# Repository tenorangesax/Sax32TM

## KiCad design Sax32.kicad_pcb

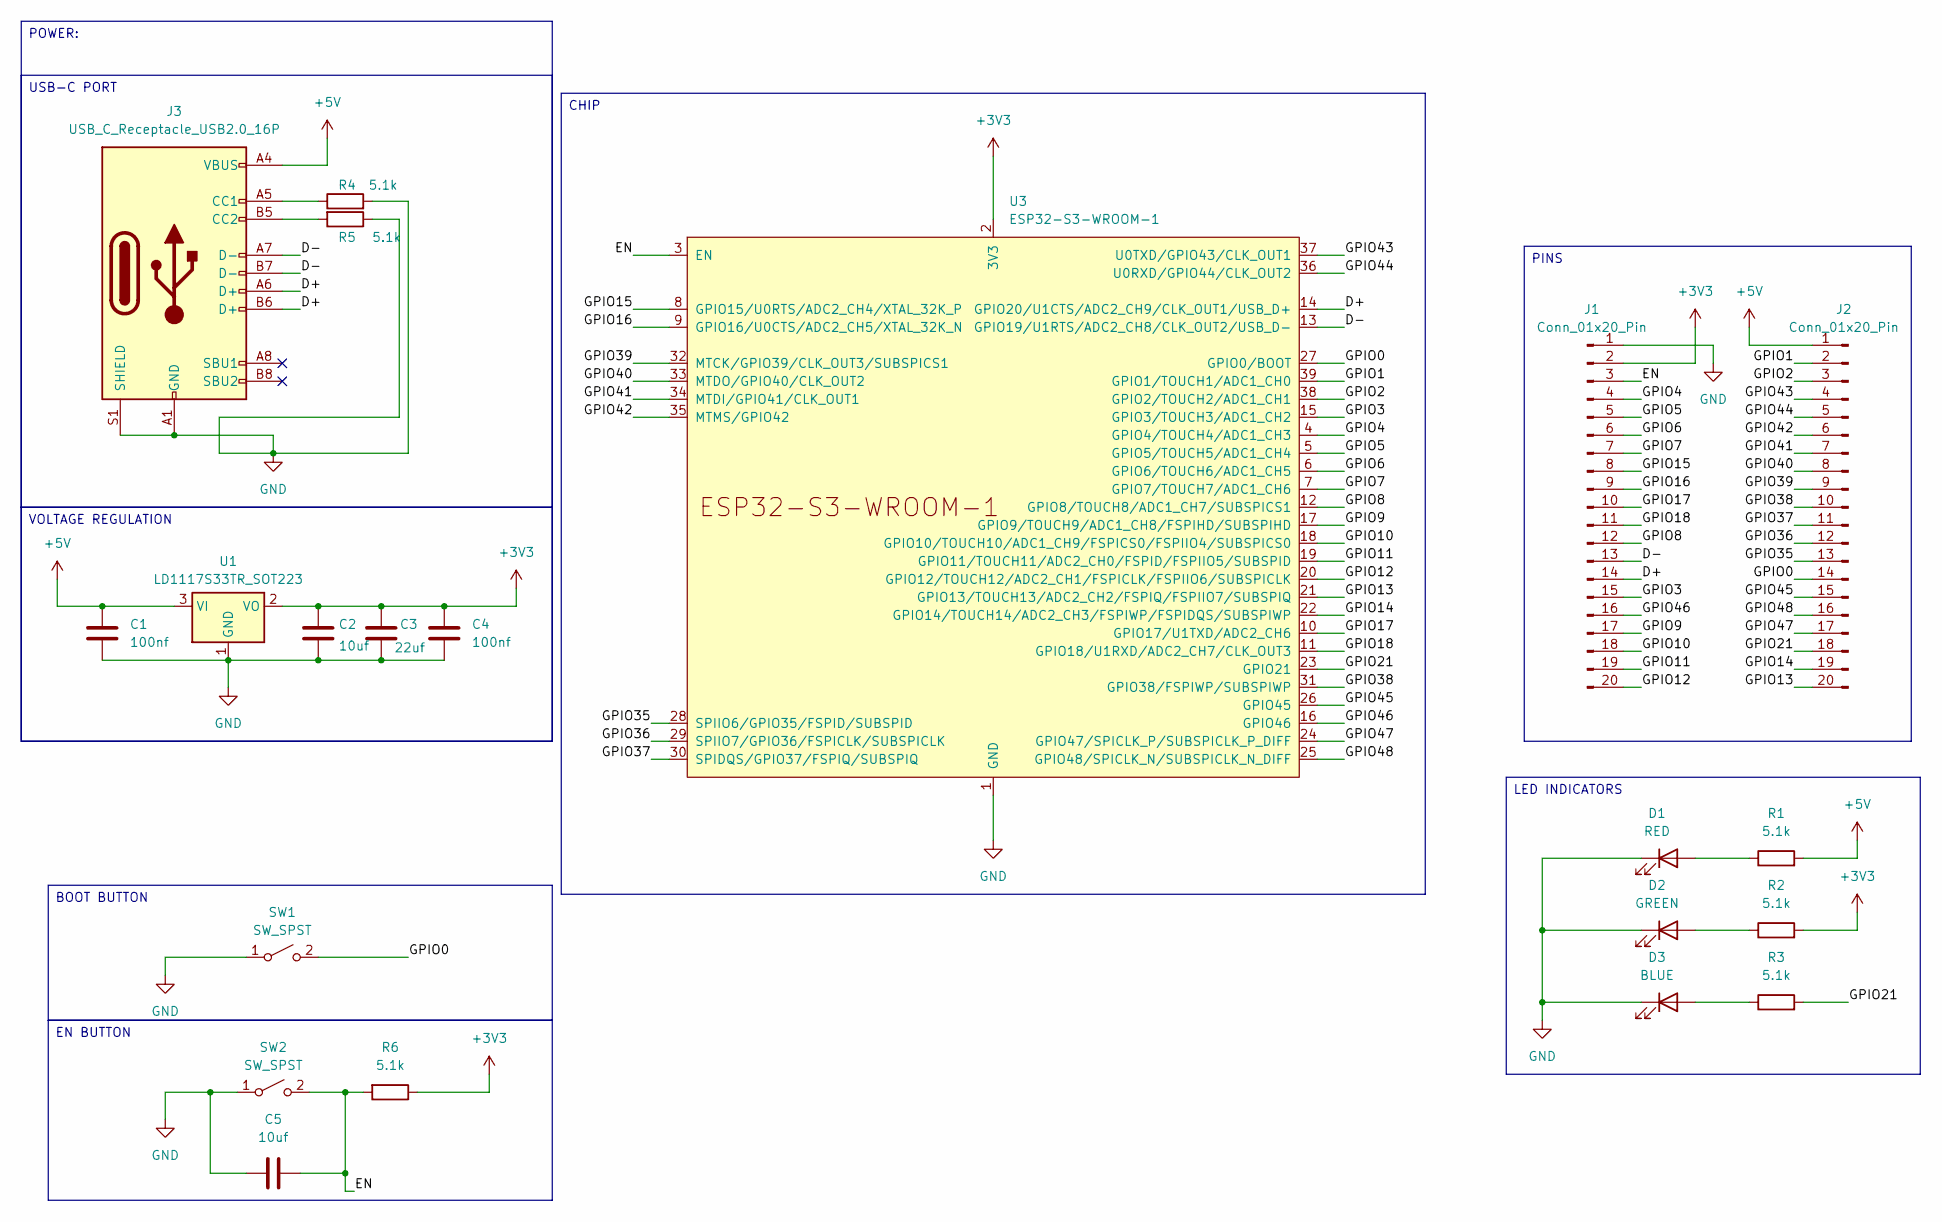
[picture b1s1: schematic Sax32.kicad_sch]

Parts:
C1, C4: 100nf; C_0603_1608Metric
C2, C5: 10uf; C_0603_1608Metric
C3: 22uf; C_0603_1608Metric
D1: RED; LED_0603_1608Metric
D2: GREEN; LED_0603_1608Metric
D3: BLUE; LED_0603_1608Metric
J1, J2: Conn_01x20_Pin; PinHeader_1x20_P2.54mm_Vertical
J3: USB_C_Receptacle_USB2.0_16P; USB_C_Receptacle_HRO_TYPE-C-31-M-12
R1, R2, R3, R4, R5, R6: 5.1k; R_0603_1608Metric
SW1, SW2: SW_SPST; SW_Push_SPST_NO_Alps_SKRK
U1: LD1117S33TR_SOT223; SOT-223-3_TabPin2
U3: ESP32-S3-WROOM-1

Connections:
+3V3: C2.1, C3.1, C4.1, J1.2, R2.2, R6.1, U1.2 (VO), U3.2 (3V3)
+5V: C1.1, J2.1, J3.A4 (VBUS), J3.A9 (VBUS), J3.B4 (VBUS), J3.B9 (VBUS), R1.2, U1.3 (VI)
/D+: J1.14, J3.A6 (D+), J3.B6 (D+), U3.14 (GPIO20/U1CTS/ADC2_CH9/CLK_OUT1/USB_D+)
/D-: J1.13, J3.A7 (D-), J3.B7 (D-), U3.13 (GPIO19/U1RTS/ADC2_CH8/CLK_OUT2/USB_D-)
/EN: C5.2, J1.3, R6.2, SW2.2 (B), U3.3 (EN)
/GPIO0: J2.14, SW1.2 (B), U3.27 (GPIO0/BOOT)
/GPIO1: J2.2, U3.39 (GPIO1/TOUCH1/ADC1_CH0)
/GPIO2: J2.3, U3.38 (GPIO2/TOUCH2/ADC1_CH1)
/GPIO3: J1.15, U3.15 (GPIO3/TOUCH3/ADC1_CH2)
/GPIO4: J1.4, U3.4 (GPIO4/TOUCH4/ADC1_CH3)
/GPIO5: J1.5, U3.5 (GPIO5/TOUCH5/ADC1_CH4)
/GPIO6: J1.6, U3.6 (GPIO6/TOUCH6/ADC1_CH5)
/GPIO7: J1.7, U3.7 (GPIO7/TOUCH7/ADC1_CH6)
/GPIO8: J1.12, U3.12 (GPIO8/TOUCH8/ADC1_CH7/SUBSPICS1)
/GPIO9: J1.17, U3.17 (GPIO9/TOUCH9/ADC1_CH8/FSPIHD/SUBSPIHD)
/GPIO10: J1.18, U3.18 (GPIO10/TOUCH10/ADC1_CH9/FSPICS0/FSPIIO4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)
/GPIO11: J1.19, U3.19 (GPIO11/TOUCH11/ADC2_CH0/FSPID/FSPIIO5/S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)
/GPIO12: J1.20, U3.20 (GPIO12/TOUCH12/ADC2_CH1/FSPICLK/FSPIIO6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)
/GPIO13: J2.20, U3.21 (GPIO13/TOUCH13/ADC2_CH2/FSPIQ/FSPIIO7/S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)
/GPIO14: J2.19, U3.22 (GPIO14/TOUCH14/ADC2_CH3/FSPIWP/FSPIDQS/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)
/GPIO15: J1.8, U3.8 (GPIO15/U0RTS/ADC2_CH4/XTAL_32K_P)
/GPIO16: J1.9, U3.9 (GPIO16/U0CTS/ADC2_CH5/XTAL_32K_N)
/GPIO17: J1.10, U3.10 (GPIO17/U1TXD/ADC2_CH6)
/GPIO18: J1.11, U3.11 (GPIO18/U1RXD/ADC2_CH7/CLK_OUT3)
/GPIO21: J2.18, R3.2, U3.23 (GPIO21)
/GPIO35: J2.13, U3.28 (SPIIO6/GPIO35/FSPID/SUBSPID)
/GPIO36: J2.12, U3.29 (SPIIO7/GPIO36/FSPICLK/SUBSPICLK)
/GPIO37: J2.11, U3.30 (SPIDQS/GPIO37/FSPIQ/SUBSPIQ)
/GPIO38: J2.10, U3.31 (GPIO38/FSPIWP/SUBSPIWP)
/GPIO39: J2.9, U3.32 (MTCK/GPIO39/CLK_OUT3/SUBSPICS1)
/GPIO40: J2.8, U3.33 (MTDO/GPIO40/CLK_OUT2)
/GPIO41: J2.7, U3.34 (MTDI/GPIO41/CLK_OUT1)
/GPIO42: J2.6, U3.35 (MTMS/GPIO42)
/GPIO43: J2.4, U3.37 (U0TXD/GPIO43/CLK_OUT1)
/GPIO44: J2.5, U3.36 (U0RXD/GPIO44/CLK_OUT2)
/GPIO45: J2.15, U3.26 (GPIO45)
/GPIO46: J1.16, U3.16 (GPIO46)
/GPIO47: J2.17, U3.24 (GPIO47/SPICLK_P/SUBSPICLK_P_DIFF)
/GPIO48: J2.16, U3.25 (GPIO48/SPICLK_N/SUBSPICLK_N_DIFF)
GND: C1.2, C2.2, C3.2, C4.2, C5.1, D1.1 (K), D2.1 (K), D3.1 (K), J1.1, J3.A1 (GND), J3.A12 (GND), J3.B1 (GND), J3.B12 (GND), J3.S1 (SHIELD), R4.2, R5.1, SW1.1 (A), SW2.1 (A), U1.1 (GND), U3.1 (GND), U3.40 (GND), U3.41 (GND)
unnamed: D1.2 (A), R1.1
unnamed: D2.2 (A), R2.1
unnamed: D3.2 (A), R3.1
unnamed: J3.A5 (CC1), R4.1
unnamed: J3.B5 (CC2), R5.2

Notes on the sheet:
VOLTAGE REGULATION
PINS
POWER:
EN BUTTON
LED INDICATORS
USB-C PORT
BOOT BUTTON
CHIP

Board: 2 copper layers, 21 parts (0 on the bottom side), 45 nets, no tracks yet.

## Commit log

2026-06-14 Create dghf
2026-06-14 Create sdfsfd
2026-06-14 Create sf
